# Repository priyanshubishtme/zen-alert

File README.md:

# ZenAlert — SIH26178 Early-Warning Dashboard Demo

A presentation-ready browser prototype for the ZenAlert environmental early-warning platform, with a FastAPI service, responsive dashboard, and focused sensor-node simulation.

## Hardware & PCB Design

ZenAlert features a custom 2-layer PCB designed in KiCad for an autonomous environmental safety and early-warning node powered by an ESP32-S2 microcontroller.

| PCB Layout (Top & Bottom Layers) | Schematic Design |
|---|---|
|  |  |

| Layer Routing Detail | Hardware Wiring & Simulation |
|---|---|
|  |  |

### PCB Specifications & Features
- **Microcontroller**: ESP32-S2 Mini
- **Board Dimensions**: 65 mm × 55 mm (2-layer FR4, 1.6 mm thickness)
- **Sensors Integrated**:
  - `MQ-135` Air Quality / Toxic Gas Sensor (GPIO1)
  - `MQ-2` Smoke & Combustible Gas Sensor (GPIO2)
  - `DHT22` Digital Temperature & Humidity Sensor (GPIO4 with 10kΩ pull-up)
- **Local Telemetry & Actuation**:
  - `SSD1306` 0.96" OLED Display (I2C: SDA GPIO8, SCL GPIO9)
  - Tri-color status indicators: Green (Safe, GPIO15), Yellow (Warning, GPIO16), Red (Critical, GPIO17)
  - High-decibel Active Alarm Buzzer (GPIO18)
  - Expansion Header for external I2C environmental modules
- **PCB Design & Fabrication Files**:
  - KiCad Schematic: [`pcb/zenalert_node.kicad_sch`](pcb/zenalert_node.kicad_sch)
  - KiCad PCB Layout: [`pcb/zenalert_node.kicad_pcb`](pcb/zenalert_node.kicad_pcb)
  - KiCad Project: [`pcb/zenalert_node.kicad_pro`](pcb/zenalert_node.kicad_pro)
  - Production Gerber Files: [`pcb/gerbers.zip`](pcb/gerbers.zip)
  - Bill of Materials: [`bom.csv`](bom.csv)

- Live Map control-room dashboard (MapLibre GL + OpenFreeMap vector tiles — no API key needed)
- Simulated environmental sensor telemetry
- Multi-modal confidence / severity display
- Incident Center with search
- Sensors & Air page
- Device Health page for 16 nodes
- Alert Composer + delivery log
- Analytics & Reports view
- Admin / thresholds page
- Standalone Sensor Node Prototype with live fire-event simulation (Three.js 3D scene)
- Dark / light mode
- English / Hindi toggle
- Online / Offline connection state
- Responsive layouts for desktop, laptop, tablet, and mobile

## Run Locally

1. Install the Python dependencies used by the backend.
2. Start the backend from the repository root:

   ```powershell
   uvicorn backend.main:app --reload --host 127.0.0.1 --port 8000
   ```

3. Open `http://127.0.0.1:8000/` for the landing page and `http://127.0.0.1:8000/app.html` for the dashboard.
4. Use the dashboard's **Prototype** page for the embedded simulation, or open `http://127.0.0.1:8000/simulation.html?v=5` for the focused standalone prototype.
5. The standalone prototype intentionally has no "Back to Site" or "Open Dashboard" actions. It is a focused sensor-node lab view containing only the simulation, sensor controls, status display, and pipeline. The dashboard embed provides the separate **Open Fullscreen** action when a larger view is needed.
6. In the dashboard, **LIVE** uses the FastAPI service and **DEMO** uses sample data. Use **EN | हिं** for the language toggle and the moon icon for theme changes.

### Prototype controls

The standalone sensor-node prototype starts in a safe state:

- **NORMAL** restores baseline telemetry and clears the camera panel.
- **FIRE TEST** runs the complete event pipeline: sensor anomaly, camera verification, AI fusion, local alarm, LoRa transmission, and dashboard notification.
- **CLEAR** returns the simulation to its initial safe state.

The prototype header is intentionally compact and contains no navigation links. It is designed to work at laptop and mobile widths. On smaller screens, the 3D scene appears first and the sensor controls follow below it; the pipeline wraps into readable rows instead of forcing horizontal scrolling.

### Final prototype UX

- The standalone page opens directly into the sensor-node simulation.
- Navigation back to the landing page and dashboard is intentionally omitted to avoid competing actions.
- The dashboard's Prototype route remains the entry point when the simulation needs to be viewed in context.
- The standalone simulation is safe by default and provides explicit **NORMAL**, **FIRE TEST**, and **CLEAR** controls.

## Deploy to Production (Render)

We deploy on **Render** as a single web service — FastAPI serves both the API and the static frontend.

1. Push this repository to GitHub.
2. Go to [Render Dashboard → Blueprints](https://dashboard.render.com/blueprints) → **New Blueprint Instance**.
3. Connect your GitHub repository — Render will detect `render.yaml` and create the service.
4. Set `FRONTEND_ORIGINS` to your Render URL (e.g. `https://zenalert-api.onrender.com`).
5. Wait for the build to finish. Your site is live at your Render URL.

See [DEPLOYMENT.md](DEPLOYMENT.md) for the full deployment guide, environment variables reference, verification checklist, and 3D map setup details.

## Map & 3D Setup — No API Keys Needed

| Component          | Library          | API Key? |
|--------------------|------------------|----------|
| Live Threat Map    | MapLibre GL JS   | ❌ No    |
| Base map tiles     | OpenFreeMap Dark (Vector) | ❌ No    |
| 3D Sensor Sim      | Three.js         | ❌ No    |

The map uses free OpenFreeMap dark vector tiles over MapLibre GL with 45° pitch for the 3D perspective. No API keys or accounts are required. See [DEPLOYMENT.md](DEPLOYMENT.md#3d-map-setup-maplibre-gl--openfreemap-tiles) for details on switching to other vector tiles (MapTiler, Stadia, Mapbox) if needed.

## Environment Setup

Copy `.env.example` to `.env` and fill in the values:

```bash
cp .env.example .env
```

See [.env.example](.env.example) for all available variables and documentation.

> **Note:** The current demo works with zero configuration. `.env` is only needed if you want to set custom CORS origins for production.

## Deployment Strategy & Scalability (Nainital Example)

Our deployment model scales cost-effectively from a single prototype to full district-wide coverage:

1. **Prototype (Bhowali Range):** 1 Gateway + 1 Node (~₹20,000) covering 5-10 km².
2. **Small Cluster:** 1 Gateway + 15 Nodes (~₹65K - 1.15L) covering 50-100 km².
3. **Priority Zones:** 8 Gateways + 80-160 Nodes (~₹5.2L - 9.2L) targeting 8 major fire-prone ranges (Naina, Kosi, etc.).
4. **Selective District Coverage:** 30-50 Gateways + 300-1000 Nodes (~₹19.5L - 57.5L) covering 10-30% of the district's 2,866 km² forest area.

## Architecture

The visual IA follows the PRD's specified dashboard pages and core features:
Live Map, Incident Center, Incident Detail, Sensors & Air Quality, Device Health, Alerts, Analytics, Admin, Public Alert View, and the Deployment Strategy page.

The map uses MapLibre GL JS with OpenFreeMap dark vector tiles; it can later be swapped for other vector tiles with a provider API key, while keeping the same UI shell.

## Backend integration points

The dashboard uses the FastAPI service when it is running and retains simulated fallback data for presentation. Replace or extend the API functions in `frontend/js/api.js` with:
- FastAPI REST calls
- FastAPI WebSocket/SSE for real-time events
- SQLite/PostgreSQL for telemetry and incidents
- MQTT/LoRa gateway data
- YOLOv8 / CNN-LSTM inference outputs
- Local image evidence from the gateway
- Alert gateways (SMS/push/siren/CAP feed)

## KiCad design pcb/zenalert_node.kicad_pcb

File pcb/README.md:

# ZenAlert — Environmental Safety Node PCB

Custom 2-layer PCB designed in KiCad for the ZenAlert environmental monitoring and early-warning node.

## Overview

The ZenAlert sensor node continuously monitors ambient environmental parameters to detect smoke, hazardous gases, and rapid heat spikes indicative of early forest or industrial fires. It features local alerting (tri-color LEDs and active buzzer) as well as an OLED display for immediate on-site diagnostics.

| Schematic Design | PCB Layer Routing |
|---|---|
|  |  |

| Hardware Wiring Diagram | Wokwi Circuit Simulation |
|---|---|
|  |  |

---

## Technical Specifications

- **Controller**: ESP32-S2 Mini (DevKitM-1 pin-compatible footprint)
- **Board Dimensions**: 65 mm × 55 mm
- **Layer Count**: 2 Layers (Top Layer F.Cu, Bottom Layer B.Cu)
- **PCB Thickness**: 1.6 mm FR4
- **Copper Weight**: 1 oz (35 µm)
- **Surface Finish**: HASL with lead or ENIG
- **Silkscreen**: White over Black / Blue soldermask
- **Mounting**: 4x M3 screw holes (3.2 mm diameter) at board corners

---

## Pin Mapping & Interfacing

| Subsystem / Component | Part | Pin / Net | Description |
|---|---|---|---|
| Air Quality Sensor | MQ-135 Module | `GPIO1` | Analog output for toxic gas & air quality |
| Smoke / Gas Sensor | MQ-2 Module | `GPIO2` | Analog output for combustible gas & smoke |
| Temp & Humidity | DHT22 | `GPIO4` | 1-Wire digital signal with 10kΩ pull-up |
| Status Indicator 1 | Green LED | `GPIO15` | Normal safe operating condition |
| Status Indicator 2 | Yellow LED | `GPIO16` | Warning / elevated threshold detected |
| Status Indicator 3 | Red LED | `GPIO17` | Critical alarm triggered |
| Acoustic Alert | Active Buzzer | `GPIO18` | High-decibel audible alarm |
| Local Display | SSD1306 0.96" OLED | `GPIO8` (SDA), `GPIO9` (SCL) | I2C display for telemetry values |
| Auxiliary Expansion | 4-Pin Header | `3V3`, `GND`, `SDA`, `SCL` | External I2C sensor node expansion |

---

## Files in this Directory

- [`zenalert_node.kicad_pro`](zenalert_node.kicad_pro) — KiCad project configuration
- [`zenalert_node.kicad_sch`](zenalert_node.kicad_sch) — Complete schematic design
- [`zenalert_node.kicad_pcb`](zenalert_node.kicad_pcb) — 2-layer PCB layout and routing
- [`gerbers.zip`](gerbers.zip) — Production-ready Gerber (RS-274X) & Excellon drill archive for fabrication (JLCPCB / PCBWay compatible)
- [`gerber/`](gerber/) — Uncompressed individual Gerber layer files
- [`kicad_pcb_layout.png`](kicad_pcb_layout.png) — Top & bottom 2D render of PCB
- [`kicad_schematic.png`](kicad_schematic.png) — KiCad schematic diagram
- [`pcb_layers_routing.png`](pcb_layers_routing.png) — Top and bottom copper trace visualization
- [`wiring_diagram.png`](wiring_diagram.png) — Breadboard wiring diagram
- [`wokwi_simulation.png`](wokwi_simulation.png) — Circuit simulation screenshot

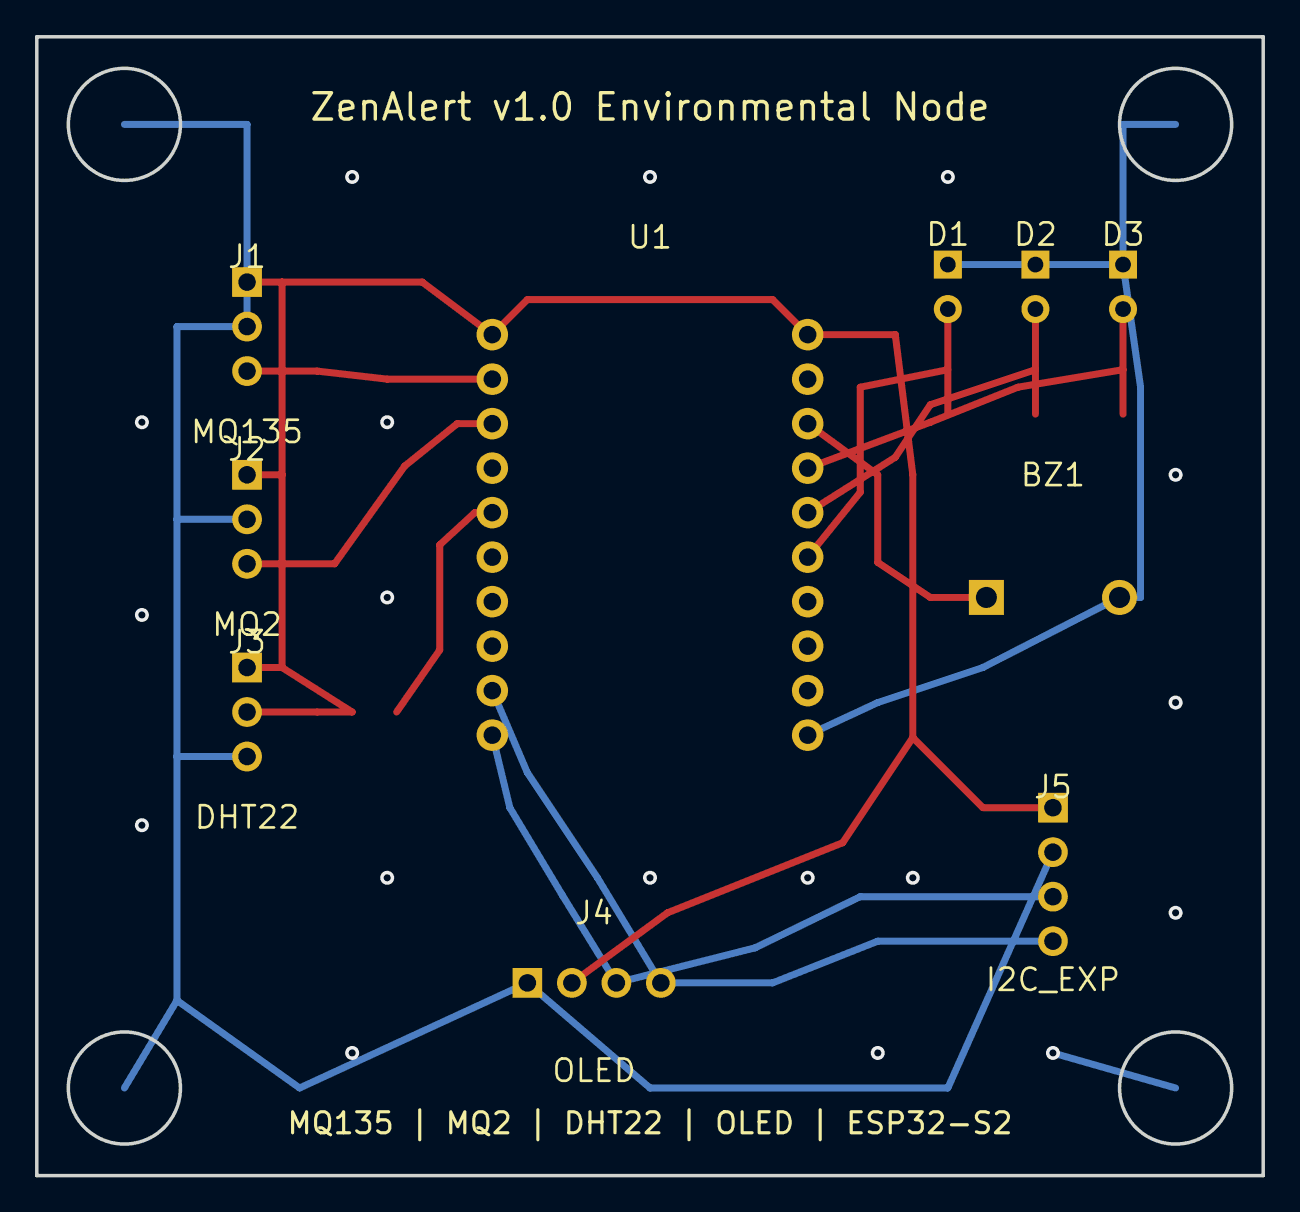
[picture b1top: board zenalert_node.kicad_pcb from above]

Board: 2 copper layers, 70.0 x 65.0 mm, 10 parts (0 on the bottom side), 11 nets.

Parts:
BZ1: Buzzer_12x9.5RM7.6
D1, D2, D3: LED_D5.0mm
J1: MQ135; PinHeader_1x03_P2.54mm
J2: MQ2; PinHeader_1x03_P2.54mm
J3: DHT22; PinHeader_1x03_P2.54mm
J4: OLED; SSD1306_OLED_0.96_I2C
J5: I2C_EXP; PinHeader_1x04_P2.54mm
U1: ESP32-S2-Mini

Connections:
+3.3V: J1.1, J2.1, J3.1, J4.2, J5.1, U1.1
BUZZER_ALARM: BZ1.1, U1.19
DHT22_DATA: J3.2, U1.5
GND: BZ1.2, D1.2, D2.2, D3.2, J1.2, J2.2, J3.3, J4.1, J5.2, U1.20
I2C_SCL: J4.3, J5.3, U1.10
I2C_SDA: J4.4, J5.4, U1.9
LED_GREEN: D1.1, U1.16
LED_RED: D3.1, U1.18
LED_YELLOW: D2.1, U1.17
MQ2_AOUT: J2.3, U1.3
MQ135_AOUT: J1.3, U1.2
